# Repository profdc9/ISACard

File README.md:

# PC Storage Interface and Arduino Inteface

This is a simple card that provides two SD cards as mass storage devices on PC compatibles in an ISA slot.  This design is an adaptation of the Apple II version of the card (<https://www.github.com/profdc9/Apple2Card>).  For building in the future, it is designed to use only the most common chips: 74HCT32, 74HCT86, 28C64B/27C128/28C256, 82C55A, and ATMEGA328P.  It does not use Compactflash format as that is a rather uncommon memory card format at the time of this writing (Oct 2025).  The SD card interface is not as fast as a Compactflash card, however, being read through SPI.  Hopefully, the components to build this board will be available for many years to come to retro enthusiasts.

There is also a 10 pin SPI port to connect an external Wiznet 5500 Ethernet port.  A simple packet driver is written to interface this to the MSDOS TCP/IP stacks as described below.

The Arduino firmware (in the ISA2Arduino directory) communicates through the 8255 bidirectional parallel port to the ISA bus.  It can expose a SD card either as a single raw block device, or it can use an image file on a FAT16/32 filesystem on the SD card as the block device.  Block device image files are named `BLKDEVXX.IMG` where XX is a hexadecimal number between 01h and 0FFh denoting the file number.  The default (and fallback) is to use `BLKDEV01.IMG` on the SD card in SLOT 1 if it is formatted for a FAT FS.  There is a MSDOS COM file called "SETBLKDV" that sets the block device number to both SD slots, with the format being:

```shell
SETBLKDV <I/O address in hex> <block device number slot 1 in hex> <block device number slot 2 in hex>.
```

For example, to set the block device to 02h on slot 1 and 0Ch on slot 2, with the card being at I/O address 0330h:

```shell
SETBLKDV 330 02 0C
```

Block device number 00h is reserved for exposing the entire SD card as a raw block device (partition table and everything) to the host.  If you do not intend for the entire card to be usable and modifiable by the host, then do not choose this option.  Most modern SD cards have a very large capacity as compared to what MSDOS is designed to handle.  SD cards with up to 8.4 GB capacity can be accommodated by C/H/S addressing using 255 heads and 63 sectors, but larger cards can be accommodated only by LBA.  Therefore larger cards are likely only to be usable by FreeDOS or another operating system designed to handle that case.

The BIOS on the card is a modified version of the XT IDE Universal BIOS with a driver added for the SD card device.  It must be configured using the xtidecfg.com program as is required by other versions of the XT IDE Universal BIOS.  As a bonus, you get the other features of the XT IDE Universal BIOS as well, and it should support the other IDE devices already in the BIOS.  The card supports up to a 32 KB ROM, with the jumpers enabling 8K, 16K, or 32K ROM sizes.  Read only and writing may also be enabled for the EEPROM so that the flash utility may work.

As with other ISA cards that use a BIOS expansion ROM (<https://minuszerodegrees.net/rom/misc/ROM%20-%20BIOS%20expansion%20ROM.jpg>), a model IBM 5150 (original IBM PC) must have a 10/27/82 dated revision of the motherboard BIOS (<https://minuszerodegrees.net/5150/bios/5150_bios_revisions.htm>), or a Compaq Portable must have at least revision C of the motherboard BIOS.

The jumpers to set the BIOS location are labeled M13 to M17 on the board so that the ROM may be located to any 8k address in the upper 0C0000h to 0FFFFFh address space.  A shorted jumpered location indicates a zero bit, and an open jumper location is a one bit.  For example, address 0D0000h (the most common XT IDE Universal BIOS address) is M17, M15, M14, M13 shorted, and M16 open. Two jumpers enable the M13 and M14 address lines to be ignored so that a larger ROM may be used.  Similarly, the IO address is marked IO2 to IO9, which may be located at any multiple of four between 000h and 3FCh.  For the default address 330h, the jumpers are set to: IO7, IO6, IO3, IO2 shorted, IO9, IO8, IO5, IO4 open.  JP17 sets the ROM size to be 32K or 8K/16K, and JP19 sets the ROM size to be 8K or 16K.  JP18 sets the ROM to be read only or ready to be flashed.

There is an ICSP connect that may be used to flash the ATMEGA328P in situ.  Make sure any SD cards are removed from the slots before flashing!  JP10 must be jumpered to power the board with the programmer.

JP9 shorts out a diode that drops the voltage on the ATMEGA328P.  Usually JP9 should be present but may be removed if there are problems with some SD cards.  J4 is a debugging connector, and J3 is a connector intended to go to a Wiznet 5500 ethernet module through a 10 position IDC cable.

## Using the ethernet capability.

A common Wiznet W5500 adapter board can be connected to the PC card using a 10 pin IDC ribbon cable.  A photograph of this board is shown below.  This adapter board has a 10 pin header on it with a pinout that corresponds to a 10 pin header marked "EXTSPI/W5500" on the card.  A 10 pin IDC ribbon cable may be used to connect the two boards.  A DOS Ethernet packet driver has been written to allow a TCP/IP stack such as MTCP (<https://www.brutman.com/mTCP/>) to be used in MSDOS which this driver has been tested with.  This packet driver has the following invocation:

```shell
ISA5500 <Software IRQ> <Hardware IRQ> <I/O Address>.
```

For example, with a software IRQ of 0x60, hardware IRQ of 3, and an I/O address of 0x330, the invocation command is:

```shell
ISA5500 0x60 3 0x330
```

Because the ethernet and SD card share the same microcontroller, they can not be used simultaneously, and the drivers take turns between mass storage calls and ethernet calls.  In order to assemble the packet driver into a COM executable, you will need an assembler like Microsoft or Turbo assembler, and the  assemble source files from the packet driver distribution (PKTD11A.ZIP PKTD11B.ZIP PKTD11C.ZIP) (<http://crynwr.com/drivers/>).   You also need to add this to the Makefile:

```makefile
isa5500.com: head.obj isa5500.obj tail.obj
	$(LINK) head isa5500 tail,isa5500/m;
	exe2com isa5500
	del isa5500.exe
```

## Licensing

The software derived from the GNU General Public License 2.0 (XT IDE Universal BIOS) is likewise licensed under the GNU General Public License 2.0 as required by the license with the modified source code being publically made available here on the GitHub.  Often software written by me is licensed under the zlib license.

The schematic designs (but not the circuit design itself) and the PCB layouts are copyrighted according to the Creative Commons 4.0 Attribution Share-Alike license.

None of these licenses should prevent anyone who wishes to reproduce this hardware and software and sell it from doing so, even for a profit.  However, source code modifications to the GPL licensed code must be made available with the product and likewise licensed under the GPLv2.

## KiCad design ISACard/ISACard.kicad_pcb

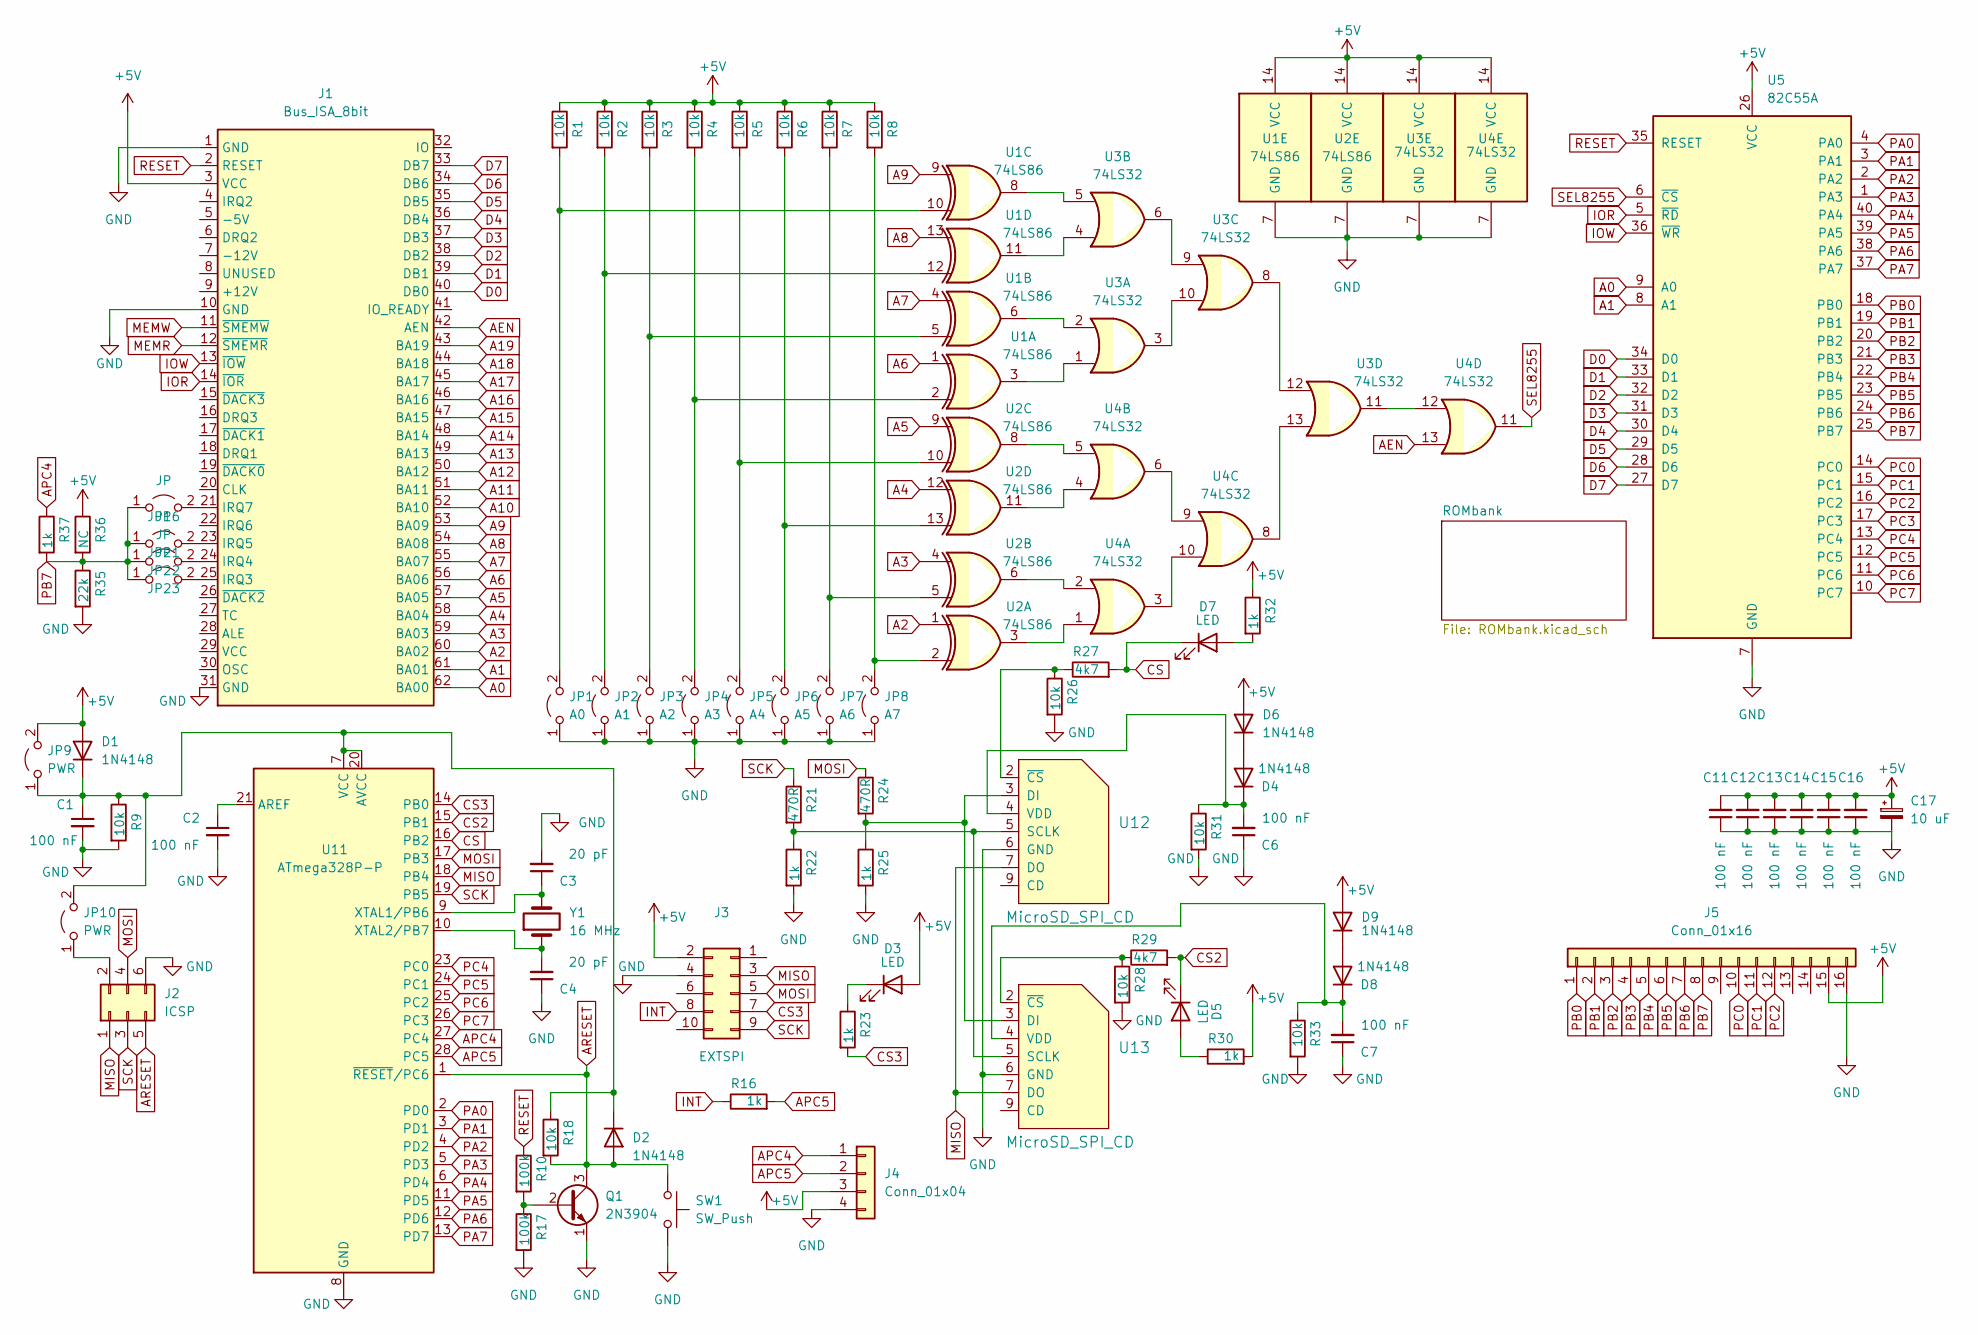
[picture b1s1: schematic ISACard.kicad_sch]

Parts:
C1, C2, C6, C7, C11, C12, C13, C14, C15, C16: 100 nF; C_Disc_D5.0mm_W2.5mm_P5.00mm
C3, C4: 20 pF; C_Disc_D5.0mm_W2.5mm_P5.00mm
C17: 10 uF; CP_Radial_D5.0mm_P2.00mm
D1, D2, D4, D6, D8, D9: 1N4148; D_DO-35_SOD27_P7.62mm_Horizontal
D3, D5, D7: LED; LED_D3.0mm
J1: Bus_ISA_8bit; BUS_ISA8
J2: ICSP; PinHeader_2x03_P2.54mm_Vertical
J3: EXTSPI; PinHeader_2x05_P2.54mm_Vertical
J4: Conn_01x04; PinHeader_1x04_P2.54mm_Vertical
J5: Conn_01x16; PinHeader_1x16_P2.54mm_Vertical
JP1: A0; PinHeader_1x02_P2.54mm_Vertical
JP2: A1; PinHeader_1x02_P2.54mm_Vertical
JP3: A2; PinHeader_1x02_P2.54mm_Vertical
JP4: A3; PinHeader_1x02_P2.54mm_Vertical
JP5: A4; PinHeader_1x02_P2.54mm_Vertical
JP6: A5; PinHeader_1x02_P2.54mm_Vertical
JP7: A6; PinHeader_1x02_P2.54mm_Vertical
JP8: A7; PinHeader_1x02_P2.54mm_Vertical
JP9, JP10: PWR; PinHeader_1x02_P2.54mm_Vertical
JP16, JP21, JP22, JP23: JP; PinHeader_1x02_P2.54mm_Vertical
Q1: 2N3904; TO-92_Inline_Wide
R1, R2, R3, R4, R5, R6, R7, R8, R9, R18, R26, R28, R31, R33: 10k; R_Axial_DIN0207_L6.3mm_D2.5mm_P7.62mm_Horizontal
R10: 100k; R_Axial_DIN0207_L6.3mm_D2.5mm_P10.16mm_Horizontal
R16, R22, R23, R25, R30, R32, R37: 1k; R_Axial_DIN0207_L6.3mm_D2.5mm_P7.62mm_Horizontal
R17: 100k; R_Axial_DIN0207_L6.3mm_D2.5mm_P7.62mm_Horizontal
R21, R24: 470R; R_Axial_DIN0207_L6.3mm_D2.5mm_P7.62mm_Horizontal
R27, R29: 4k7; R_Axial_DIN0207_L6.3mm_D2.5mm_P7.62mm_Horizontal
R35: 22k; R_Axial_DIN0207_L6.3mm_D2.5mm_P7.62mm_Horizontal
R36: NC; R_Axial_DIN0207_L6.3mm_D2.5mm_P7.62mm_Horizontal
SW1: SW_Push; SW_PUSH_6mm
U1, U2: 74LS86; DIP-14_W7.62mm_Socket
U3, U4: 74LS32; DIP-14_W7.62mm_Socket
U5: 82C55A; DIP-40_W15.24mm_Socket
U11: ATmega328P-P; DIP-28_W7.62mm_Socket
U12, U13: MicroSD_SPI_CD; GCT-MEM2055-00-190-01-A
Y1: 16 MHz; Crystal_HC49-U_Vertical

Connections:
+5V: C11.2, C12.2, C13.2, C14.2, C15.2, C16.2, C17.1, D1.2 (A), D3.2 (A), D6.2 (A), D9.2 (A), J1.3 (VCC), J3.2, J4.3, J5.15, JP9.2 (B), R1.1, R2.1, R3.1, R4.1, R5.1, R6.1, R7.1, R8.1, R30.2, R32.1, R36.1, U1.14 (VCC), U2.14 (VCC), U3.14 (VCC), U4.14 (VCC), U5.26 (VCC); also elsewhere on the board
A0: J1.62 (BA00), U5.9 (A0); also elsewhere on the board
A1: J1.61 (BA01), U5.8 (A1); also elsewhere on the board
A2: J1.60 (BA02), U2.1; also elsewhere on the board
A3: J1.59 (BA03), U2.4; also elsewhere on the board
A4: J1.58 (BA04), U2.12; also elsewhere on the board
A5: J1.57 (BA05), U2.9; also elsewhere on the board
A6: J1.56 (BA06), U1.1; also elsewhere on the board
A7: J1.55 (BA07), U1.4; also elsewhere on the board
A8: J1.54 (BA08), U1.13; also elsewhere on the board
A9: J1.53 (BA09), U1.9; also elsewhere on the board
A10: J1.52 (BA10); also elsewhere on the board
A11: J1.51 (BA11); also elsewhere on the board
A12: J1.50 (BA12); also elsewhere on the board
A13: J1.49 (BA13); also elsewhere on the board
A14: J1.48 (BA14); also elsewhere on the board
A15: J1.47 (BA15); also elsewhere on the board
A16: J1.46 (BA16); also elsewhere on the board
A17: J1.45 (BA17); also elsewhere on the board
A18: J1.44 (BA18); also elsewhere on the board
A19: J1.43 (BA19); also elsewhere on the board
AEN: J1.42 (AEN), U4.13; also elsewhere on the board
APC4: J4.1, R37.1, U11.27 (PC4)
APC5: J4.2, R16.2, U11.28 (PC5)
ARESET: D2.2 (A), J2.5, Q1.3 (C), R18.2, SW1.1, U11.1 (~RESET/PC6)
CS: D7.1 (K), R27.2, U11.16 (PB2)
CS2: D5.1 (K), R29.2, U11.15 (PB1)
CS3: J3.7, R23.2, U11.14 (PB0)
D0: J1.40 (DB0), U5.34 (D0); also elsewhere on the board
D1: J1.39 (DB1), U5.33 (D1); also elsewhere on the board
D2: J1.38 (DB2), U5.32 (D2); also elsewhere on the board
D3: J1.37 (DB3), U5.31 (D3); also elsewhere on the board
D4: J1.36 (DB4), U5.30 (D4); also elsewhere on the board
D5: J1.35 (DB5), U5.29 (D5); also elsewhere on the board
D6: J1.34 (DB6), U5.28 (D6); also elsewhere on the board
D7: J1.33 (DB7), U5.27 (D7); also elsewhere on the board
GND: C1.2, C2.2, C3.2, C4.1, C6.1, C7.1, C11.1, C12.1, C13.1, C14.1, C15.1, C16.1, C17.2, J1.1 (GND), J1.10 (GND), J1.31 (GND), J2.6, J3.4, J4.4, J5.16, JP1.1 (A), JP2.1 (A), JP3.1 (A), JP4.1 (A), JP5.1 (A), JP6.1 (A), JP7.1 (A), JP8.1 (A), Q1.1 (E), R9.2, R17.2, R22.2, R25.2, R26.2, R28.2, R31.2, R33.2, R35.2, SW1.2, U1.7 (GND), U2.7 (GND), U3.7 (GND), U4.7 (GND), U5.7 (GND), U11.8 (GND), U11.22 (GND), U12.6 (GND), U13.6 (GND); also elsewhere on the board
INT: J3.8, R16.1
IOR: J1.14 (~IOR), U5.5 (~RD)
IOW: J1.13 (~IOW), U5.36 (~WR)
MEMR: J1.12 (~SMEMR); also elsewhere on the board
MEMW: J1.11 (~SMEMW); also elsewhere on the board
MISO: J2.1, J3.3, U11.18 (PB4), U12.7 (DO), U13.7 (DO)
MOSI: J2.4, J3.5, R24.1, U11.17 (PB3)
unnamed: C1.1, D1.1 (K), D2.1 (K), JP9.1 (A), JP10.2 (B), R9.1, R18.1, U11.7 (VCC), U11.20 (AVCC)
unnamed: D3.1 (K), R23.1
unnamed: D4.2 (A), D6.1 (K)
unnamed: C6.2, D4.1 (K), R31.1, U12.4 (VDD)
unnamed: D5.2 (A), R30.1
unnamed: D7.2 (A), R32.2
unnamed: D8.2 (A), D9.1 (K)
unnamed: C7.2, D8.1 (K), R33.1, U13.4 (VDD)
unnamed: J1.25 (IRQ3), JP23.2 (B)
unnamed: J1.24 (IRQ4), JP22.2 (B)
unnamed: J1.23 (IRQ5), JP21.2 (B)
unnamed: J1.21 (IRQ7), JP16.2 (B)
unnamed: J2.2, JP10.1 (A)
unnamed: JP1.2 (B), R1.2, U1.10
unnamed: JP2.2 (B), R2.2, U1.12
unnamed: JP3.2 (B), R3.2, U1.5
unnamed: JP4.2 (B), R4.2, U1.2
unnamed: JP5.2 (B), R5.2, U2.10
unnamed: JP6.2 (B), R6.2, U2.13
unnamed: JP7.2 (B), R7.2, U2.5
unnamed: JP8.2 (B), R8.2, U2.2
unnamed: Q1.2 (B), R10.2, R17.1
unnamed: U1.3, U3.1
unnamed: U1.6, U3.2
unnamed: U1.8, U3.5
unnamed: U1.11, U3.4
unnamed: U2.3, U4.1
unnamed: U2.6, U4.2
unnamed: U2.8, U4.5
unnamed: U2.11, U4.4
unnamed: U3.6, U3.9
unnamed: U3.3, U3.10
unnamed: U3.11, U4.12
unnamed: U3.8, U3.12
unnamed: U3.13, U4.8
unnamed: U4.6, U4.9
unnamed: U4.3, U4.10
unnamed: C2.1, U11.21 (AREF)
unnamed: C3.1, U11.9 (XTAL1/PB6), Y1.2
unnamed: C4.2, U11.10 (XTAL2/PB7), Y1.1
unnamed: R24.2, R25.1, U12.3 (DI), U13.3 (DI)
unnamed: R21.2, R22.1, U12.5 (SCLK), U13.5 (SCLK)
unnamed: R26.1, R27.1, U12.2 (~CS)
unnamed: R28.1, R29.1, U13.2 (~CS)
PA0: U5.4 (PA0), U11.2 (PD0)
PA1: U5.3 (PA1), U11.3 (PD1)
PA2: U5.2 (PA2), U11.4 (PD2)
PA3: U5.1 (PA3), U11.5 (PD3)
PA4: U5.40 (PA4), U11.6 (PD4)
PA5: U5.39 (PA5), U11.11 (PD5)
PA6: U5.38 (PA6), U11.12 (PD6)
PA7: U5.37 (PA7), U11.13 (PD7)
PB0: J5.1, U5.18 (PB0)
PB1: J5.2, U5.19 (PB1)
PB2: J5.3, U5.20 (PB2)
PB3: J5.4, U5.21 (PB3)
PB4: J5.5, U5.22 (PB4)
PB5: J5.6, U5.23 (PB5)
PB6: J5.7, U5.24 (PB6)
PB7: J5.8, JP16.1 (A), JP21.1 (A), JP22.1 (A), JP23.1 (A), R35.1, R36.2, R37.2, U5.25 (PB7)
PC0: J5.10, U5.14 (PC0)
PC1: J5.11, U5.15 (PC1)
PC2: J5.12, U5.16 (PC2)
PC3: U5.17 (PC3)
PC4: U5.13 (PC4), U11.23 (PC0)
PC5: U5.12 (PC5), U11.24 (PC1)
PC6: U5.11 (PC6), U11.25 (PC2)
PC7: U5.10 (PC7), U11.26 (PC3)
RESET: J1.2 (RESET), R10.1, U5.35 (RESET)
SCK: J2.3, J3.9, R21.1, U11.19 (PB5)
SEL8255: U4.11, U5.6 (~CS)

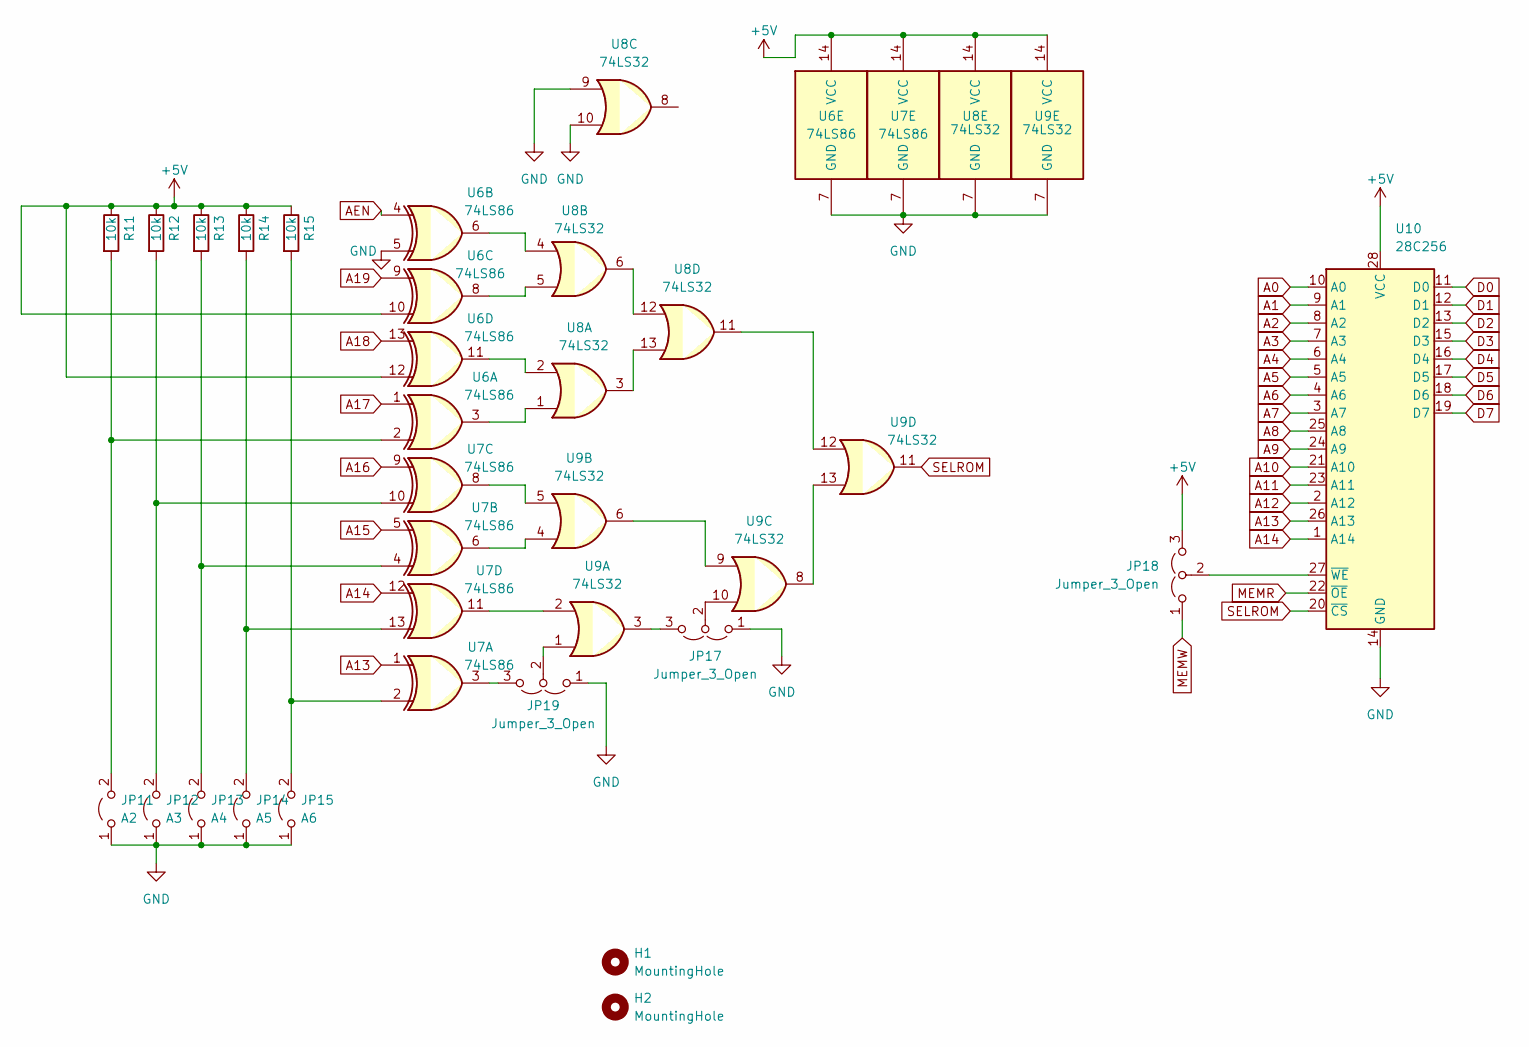
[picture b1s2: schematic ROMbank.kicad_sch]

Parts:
H1, H2: MountingHole; MountingHole_3.7mm
JP11: A2; PinHeader_1x02_P2.54mm_Vertical
JP12: A3; PinHeader_1x02_P2.54mm_Vertical
JP13: A4; PinHeader_1x02_P2.54mm_Vertical
JP14: A5; PinHeader_1x02_P2.54mm_Vertical
JP15: A6; PinHeader_1x02_P2.54mm_Vertical
JP17, JP18, JP19: Jumper_3_Open; PinHeader_1x03_P2.54mm_Vertical
R11, R12, R13, R14, R15: 10k; R_Axial_DIN0207_L6.3mm_D2.5mm_P7.62mm_Horizontal
U6, U7: 74LS86; DIP-14_W7.62mm_Socket
U8, U9: 74LS32; DIP-14_W7.62mm_Socket
U10: 28C256; DIP-28_W15.24mm_Socket

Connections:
+5V: JP18.3 (B), R11.1, R12.1, R13.1, R14.1, R15.1, U6.10, U6.12, U6.14 (VCC), U7.14 (VCC), U8.14 (VCC), U9.14 (VCC), U10.28 (VCC); also elsewhere on the board
A0: U10.10 (A0); also elsewhere on the board
A1: U10.9 (A1); also elsewhere on the board
A2: U10.8 (A2); also elsewhere on the board
A3: U10.7 (A3); also elsewhere on the board
A4: U10.6 (A4); also elsewhere on the board
A5: U10.5 (A5); also elsewhere on the board
A6: U10.4 (A6); also elsewhere on the board
A7: U10.3 (A7); also elsewhere on the board
A8: U10.25 (A8); also elsewhere on the board
A9: U10.24 (A9); also elsewhere on the board
A10: U10.21 (A10); also elsewhere on the board
A11: U10.23 (A11); also elsewhere on the board
A12: U10.2 (A12); also elsewhere on the board
A13: U7.1, U10.26 (A13); also elsewhere on the board
A14: U7.12, U10.1 (A14); also elsewhere on the board
A15: U7.5; also elsewhere on the board
A16: U7.9; also elsewhere on the board
A17: U6.1; also elsewhere on the board
A18: U6.13; also elsewhere on the board
A19: U6.9; also elsewhere on the board
AEN: U6.4; also elsewhere on the board
D0: U10.11 (D0); also elsewhere on the board
D1: U10.12 (D1); also elsewhere on the board
D2: U10.13 (D2); also elsewhere on the board
D3: U10.15 (D3); also elsewhere on the board
D4: U10.16 (D4); also elsewhere on the board
D5: U10.17 (D5); also elsewhere on the board
D6: U10.18 (D6); also elsewhere on the board
D7: U10.19 (D7); also elsewhere on the board
GND: JP11.1 (A), JP12.1 (A), JP13.1 (A), JP14.1 (A), JP15.1 (A), JP17.1 (A), JP19.1 (A), U6.5, U6.7 (GND), U7.7 (GND), U8.7 (GND), U8.9, U8.10, U9.7 (GND), U10.14 (GND); also elsewhere on the board
MEMR: U10.22 (~OE); also elsewhere on the board
MEMW: JP18.1 (A); also elsewhere on the board
unnamed: JP11.2 (B), R11.2, U6.2
unnamed: JP12.2 (B), R12.2, U7.10
unnamed: JP13.2 (B), R13.2, U7.4
unnamed: JP14.2 (B), R14.2, U7.13
unnamed: JP15.2 (B), R15.2, U7.2
unnamed: JP17.3 (B), U9.3
unnamed: JP17.2 (C), U9.10
unnamed: JP18.2 (C), U10.27 (~WE)
unnamed: JP19.3 (B), U7.3
unnamed: JP19.2 (C), U9.1
unnamed: U6.3, U8.1
unnamed: U6.6, U8.4
unnamed: U6.8, U8.5
unnamed: U6.11, U8.2
unnamed: U7.6, U9.4
unnamed: U7.8, U9.5
unnamed: U7.11, U9.2
unnamed: U8.11, U9.12
unnamed: U8.6, U8.12
unnamed: U8.3, U8.13
unnamed: U9.6, U9.9
unnamed: U9.8, U9.13
SELROM: U9.11, U10.20 (~CS)

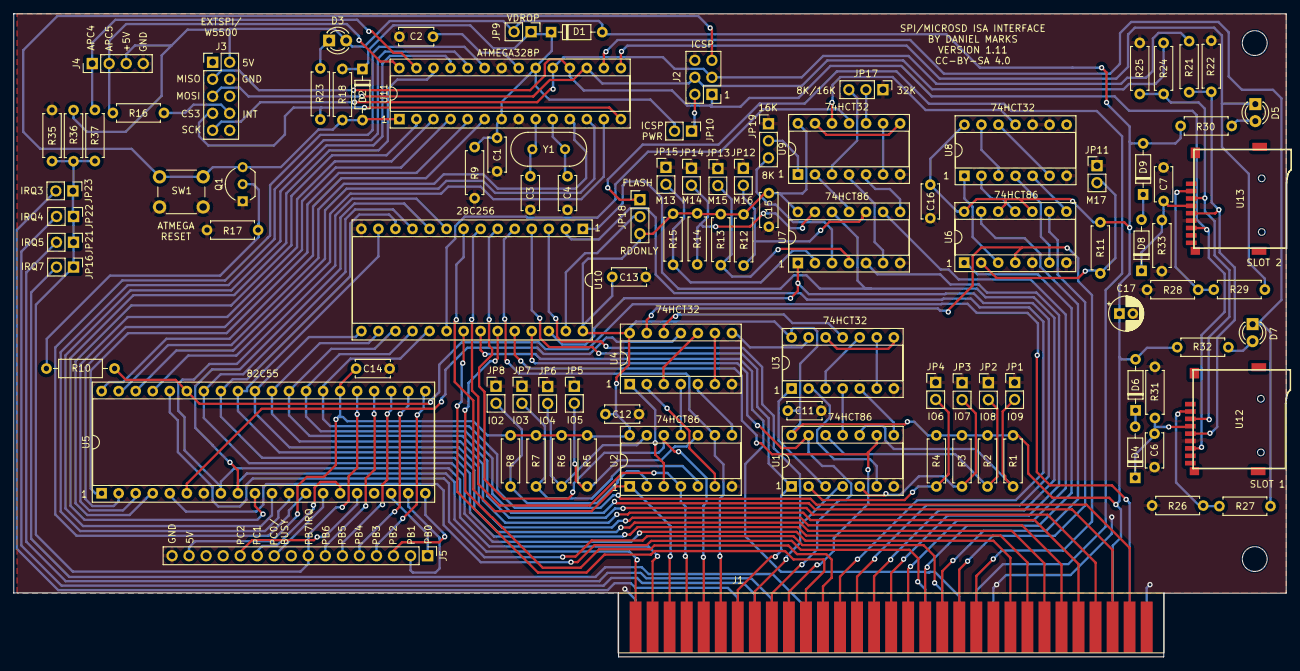
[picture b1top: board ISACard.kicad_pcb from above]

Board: 2 copper layers, 189.7 x 95.9 mm, 101 parts (0 on the bottom side), 137 nets.

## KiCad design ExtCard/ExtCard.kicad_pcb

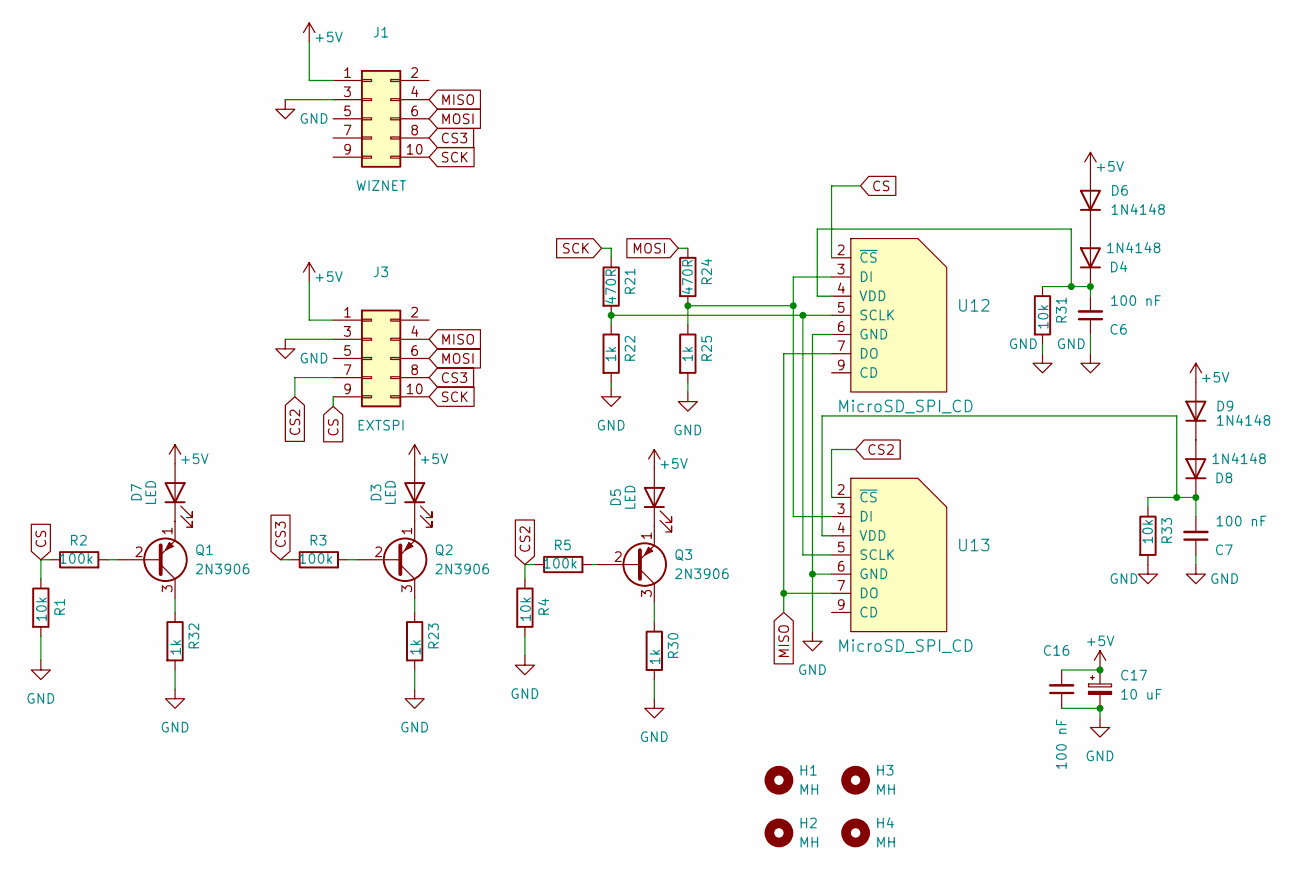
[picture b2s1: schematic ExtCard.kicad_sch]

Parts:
C6, C7, C16: 100 nF; C_Disc_D5.0mm_W2.5mm_P5.00mm
C17: 10 uF; CP_Radial_D5.0mm_P2.00mm
D3, D5, D7: LED; LED_D3.0mm
D4, D6, D8, D9: 1N4148; D_DO-35_SOD27_P7.62mm_Horizontal
H1, H2, H3, H4: MH; MountingHole_3.2mm_M3
J1: WIZNET; PinHeader_2x05_P2.54mm_Vertical
J3: EXTSPI; PinHeader_2x05_P2.54mm_Vertical
Q1, Q2, Q3: 2N3906; TO-92_Inline_Wide
R1, R4, R31, R33: 10k; R_Axial_DIN0207_L6.3mm_D2.5mm_P7.62mm_Horizontal
R2, R3, R5: 100k; R_Axial_DIN0207_L6.3mm_D2.5mm_P7.62mm_Horizontal
R21, R24: 470R; R_Axial_DIN0207_L6.3mm_D2.5mm_P7.62mm_Horizontal
R22, R23, R25, R30, R32: 1k; R_Axial_DIN0207_L6.3mm_D2.5mm_P7.62mm_Horizontal
U12, U13: MicroSD_SPI_CD; GCT-MEM2055-00-190-01-A

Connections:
+5V: C16.2, C17.1, D3.2 (A), D5.2 (A), D6.2 (A), D7.2 (A), D9.2 (A), J1.1, J3.1
CS: J3.9, R1.1, R2.1, U12.2 (~CS)
CS2: J3.7, R4.1, R5.1, U13.2 (~CS)
CS3: J1.8, J3.8, R3.1
GND: C6.1, C7.1, C16.1, C17.2, J1.3, J3.3, R1.2, R4.2, R22.2, R23.2, R25.2, R30.2, R31.2, R32.2, R33.2, U12.6 (GND), U13.6 (GND)
MISO: J1.4, J3.4, U12.7 (DO), U13.7 (DO)
MOSI: J1.6, J3.6, R24.1
unnamed: C6.2, D4.1 (K), R31.1, U12.4 (VDD)
unnamed: C7.2, D8.1 (K), R33.1, U13.4 (VDD)
unnamed: D4.2 (A), D6.1 (K)
unnamed: D5.1 (K), Q3.1 (E)
unnamed: D8.2 (A), D9.1 (K)
unnamed: D7.1 (K), Q1.1 (E)
unnamed: Q1.2 (B), R2.2
unnamed: Q1.3 (C), R32.1
unnamed: D3.1 (K), Q2.1 (E)
unnamed: Q2.2 (B), R3.2
unnamed: Q2.3 (C), R23.1
unnamed: Q3.2 (B), R5.2
unnamed: Q3.3 (C), R30.1
unnamed: R21.2, R22.1, U12.5 (SCLK), U13.5 (SCLK)
unnamed: R24.2, R25.1, U12.3 (DI), U13.3 (DI)
SCK: J1.10, J3.10, R21.1

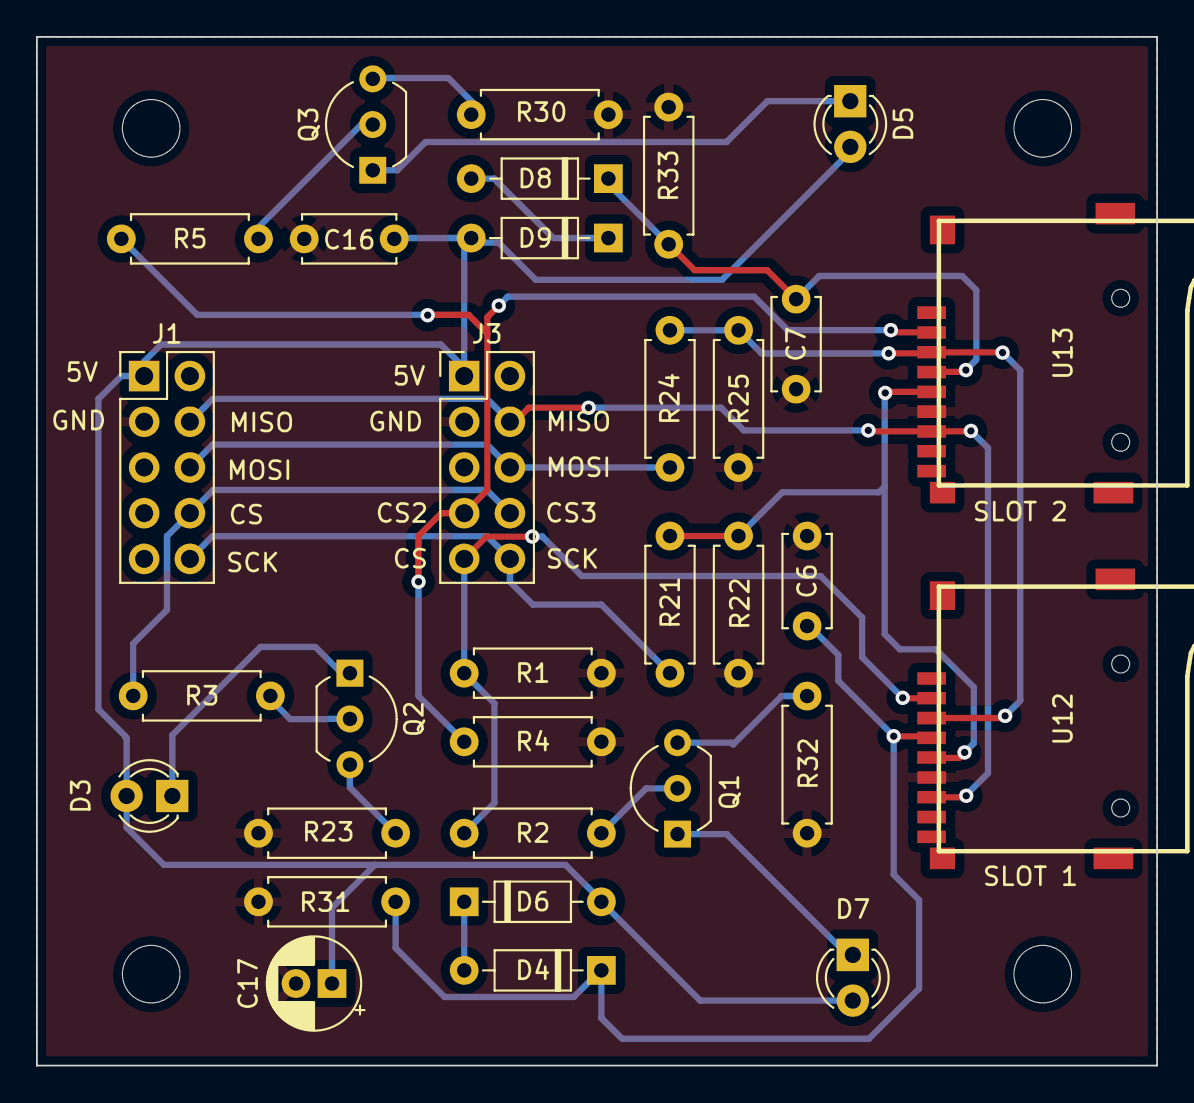
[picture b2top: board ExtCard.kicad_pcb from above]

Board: 2 copper layers, 62.2 x 57.2 mm, 36 parts (0 on the bottom side), 23 nets.

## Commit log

2022-06-23 Added labels
2022-06-23 Added gerber files and CS/CS2 to feature connector
2022-06-24 Added external SD card board
2022-06-24 Moved around some traces
2022-07-08 Added 16k/32k jumper
2025-09-19 working on xt ide universal bios mod
2025-09-20 First stab at bios
2025-09-21 Added to ROM configurator
2025-09-22 Fixed SDServer, configuration
2025-09-23 fixed sd server scan jump point
2025-09-24 Fixed some problems with the card...
2025-09-24 Rearranged the order of the logic
2025-09-26 fixed rom labels
2025-09-29 first commit ISA2Arduino
2025-10-01 first working version
2025-10-02 fixed ID bit
2025-10-03 added documentation
2025-10-04 Added setblkdv command
2025-10-06 modified README.md
2025-10-06 moved SD card slots to edge
2025-10-06 Moved ATMEGA328P so that trace length is shorter
2025-10-08 minor pcb tweaks
2025-10-12 Added licensing information
2025-10-14 Added IRQ connection to ethernet
2025-10-14 Adjusted bias of resistors
2025-10-21 modified IRQ system
2025-10-22 Added C0 bit set for interrupt tracking
2025-10-22 Added IRQ response bit to determine spurious interrupt
2025-11-15 Improve Markdown formatting
    * Remove trailing spaces.
    * Fix linter warnings: "bare URL used".
    * Add code blocks.
    * Add dedicated header for a licensing part of README.
2025-11-15 Rename license files to have prefix "LICENSE", so GitHub recognise them properly and display in the right top corner "About"
2025-11-18 Send to JLCPCB
2025-11-26 Prepared for ethernet debugging
2025-12-20 First version of packet driver
2025-12-21 ISACard modification
2025-12-21 Double directory
2025-12-23 Modified README

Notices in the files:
ISACard/ISACard.kicad_pcb:
CC-BY-SA 4.0
